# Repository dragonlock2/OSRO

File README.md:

# OSRO (Open-Source Reflow Oven)

OSRO is an ESP32-C3 powered WiFi-connected reflow oven controller designed for low cost and ease of use. Web UI is built on React JS for those aesthetics.

## Building

1. Build the web UI.
```
cd webui
npm install
npm run build
```
2. Follow the [instructions](https://docs.espressif.com/projects/esp-idf/en/latest/esp32/get-started/) to get ESP-IDF set up. Currently tested with ESP-IDF `v5.0.2`.
3. Setup the build for the firmware. Make sure to set the WiFi SSID and password under `OSRO WiFi configuration`.
```
cd firmware
get_idf
idf.py set-target esp32c3
idf.py menuconfig
```
4. Build and flash the firmware.
```
cd firmware
idf.py build
idf.py -p <serial port> flash
```

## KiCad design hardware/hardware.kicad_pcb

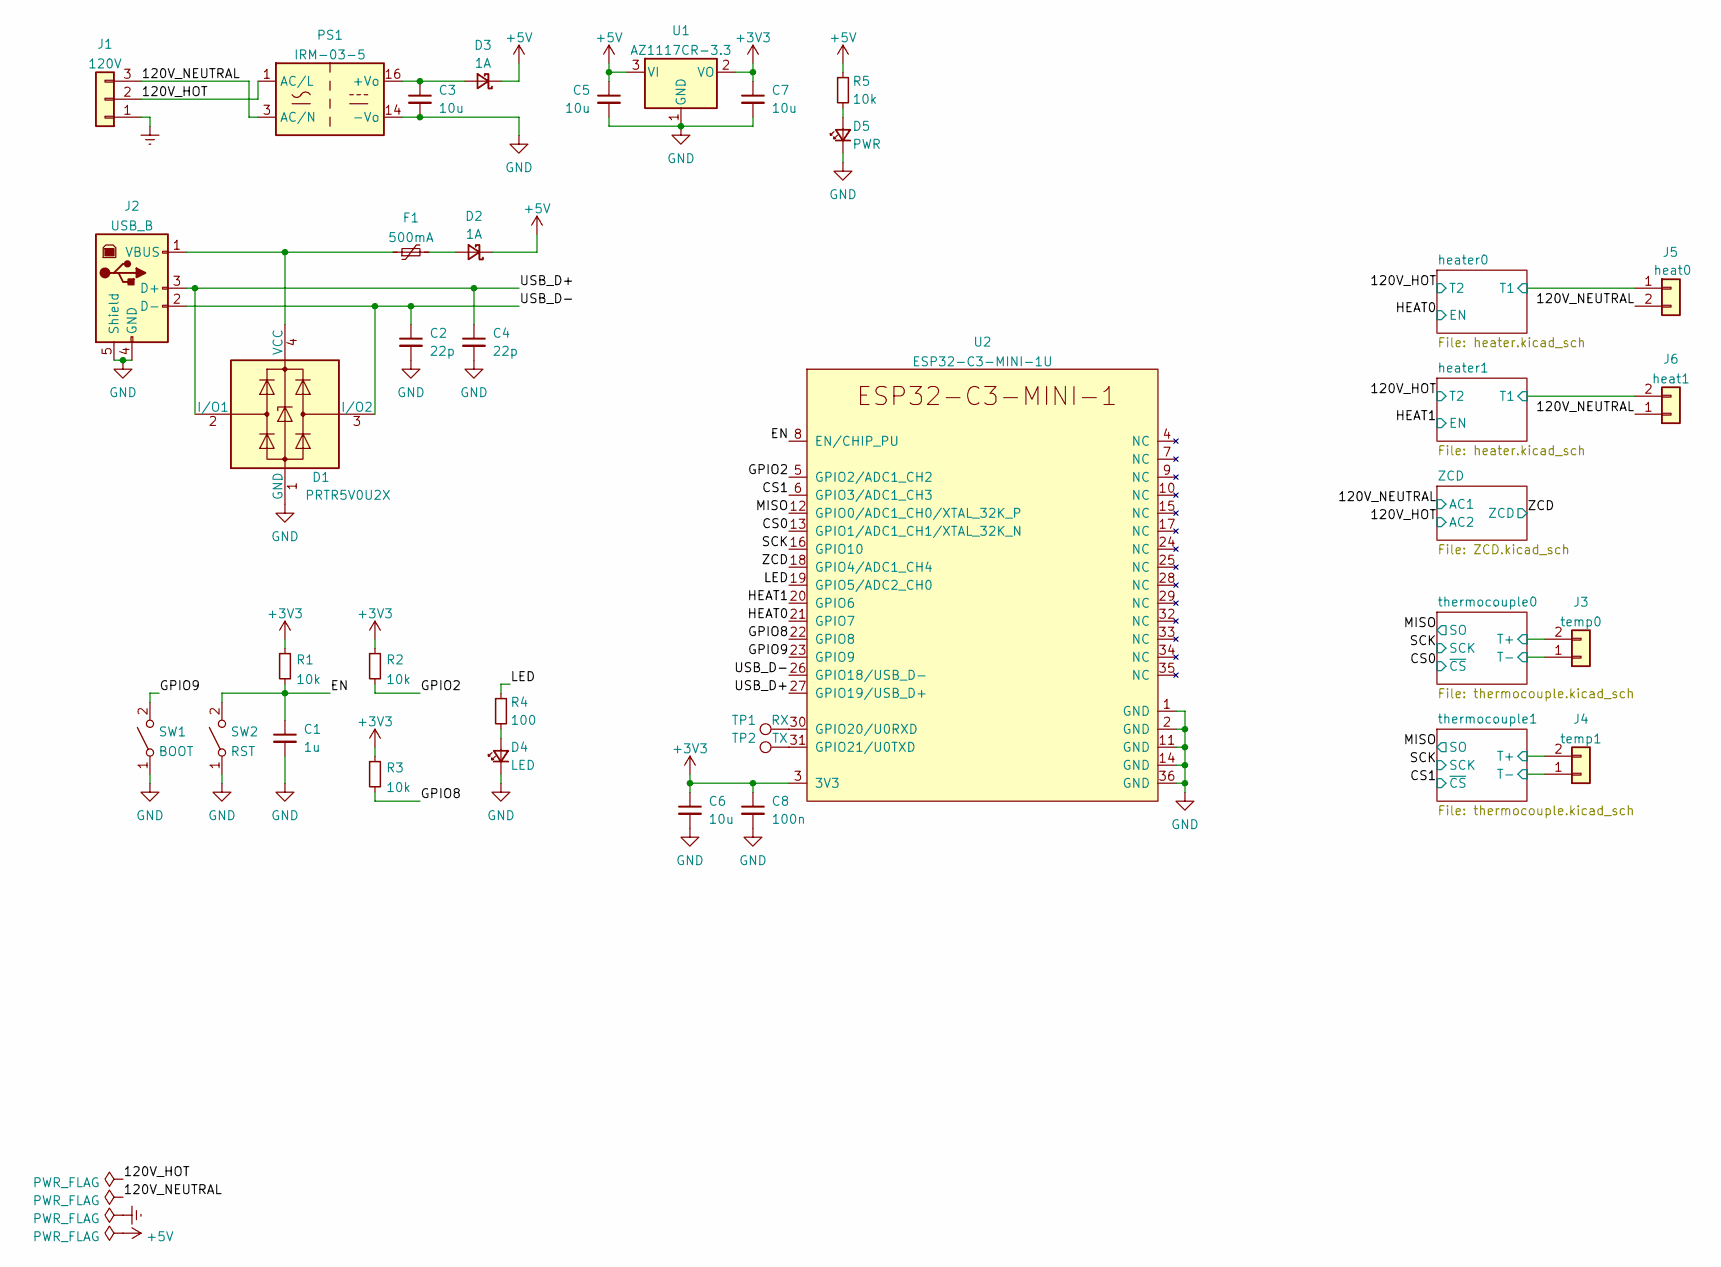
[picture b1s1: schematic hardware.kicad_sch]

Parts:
C1: 1u; C_0603_1608Metric
C2, C4: 22p; C_0603_1608Metric
C3, C5, C6, C7: 10u; C_0805_2012Metric
C8: 100n; C_0603_1608Metric
D1: PRTR5V0U2X; SOT-143
D2, D3: 1A; D_SOD-123F
D4: LED; LED_0603_1608Metric
D5: PWR; LED_0603_1608Metric
F1: 500mA; Fuse_1206_3216Metric
J1: 120V; Molex_MicroFit+_RH_1row_3pin
J2: USB_B; USB_B_TE_5787834_Vertical
J3: temp0; Molex_DuraClik_RH_2pin
J4: temp1; Molex_DuraClik_RH_2pin
J5: heat0; Molex_MicroFit+_RH_1row_2pin
J6: heat1; Molex_MicroFit+_RH_1row_2pin
PS1: IRM-03-5; Converter_ACDC_MeanWell_IRM-03-xx_THT
R1, R2, R3, R5: 10k; R_0603_1608Metric
R4: 100; R_0603_1608Metric
SW1: BOOT; SW_SPST_PTS810
SW2: RST; SW_SPST_PTS810
TP1: RX; TestPoint_Pad_D2.0mm
TP2: TX; TestPoint_Pad_D2.0mm
U1: AZ1117CR-3.3; SOT-89-3
U2: ESP32-C3-MINI-1U

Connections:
+3V3: C6.1, C7.1, C8.1, R1.1, R2.1, R3.1, U1.2 (VO), U2.3 (3V3); also elsewhere on the board
+5V: C5.1, D2.1 (K), D3.1 (K), R5.1, U1.3 (VI)
/120V_HOT: J1.2, PS1.1 (AC/L); also elsewhere on the board
/120V_NEUTRAL: J1.3, J5.2, J6.1, PS1.3 (AC/N); also elsewhere on the board
/CS0: U2.13 (GPIO1/ADC1_CH1/XTAL_32K_N); also elsewhere on the board
/CS1: U2.6 (GPIO3/ADC1_CH3); also elsewhere on the board
/EN: C1.1, R1.2, SW2.2 (B), U2.8 (EN/CHIP_PU)
/GPIO2: R2.2, U2.5 (GPIO2/ADC1_CH2)
/GPIO8: R3.2, U2.22 (GPIO8)
/GPIO9: SW1.2 (B), U2.23 (GPIO9)
/HEAT0: U2.21 (GPIO7); also elsewhere on the board
/HEAT1: U2.20 (GPIO6); also elsewhere on the board
/LED: R4.1, U2.19 (GPIO5/ADC2_CH0)
/MISO: U2.12 (GPIO0/ADC1_CH0/XTAL_32K_P); also elsewhere on the board
/SCK: U2.16 (GPIO10); also elsewhere on the board
/USB_D+: C4.1, D1.2 (I/O1), J2.3 (D+), U2.27 (GPIO19/USB_D+)
/USB_D-: C2.1, D1.3 (I/O2), J2.2 (D-), U2.26 (GPIO18/USB_D-)
/ZCD: U2.18 (GPIO4/ADC1_CH4); also elsewhere on the board
/heater0/T1: J5.1; also elsewhere on the board
/heater1/T1: J6.2; also elsewhere on the board
/thermocouple0/T+: J3.2; also elsewhere on the board
/thermocouple0/T-: J3.1; also elsewhere on the board
/thermocouple1/T+: J4.2; also elsewhere on the board
/thermocouple1/T-: J4.1; also elsewhere on the board
Earth: J1.1
GND: C1.2, C2.2, C3.2, C4.2, C5.2, C6.2, C7.2, C8.2, D1.1 (GND), D4.1 (K), D5.1 (K), J2.4 (GND), J2.5 (Shield), PS1.14 (-Vo), SW1.1 (A), SW2.1 (A), U1.1 (GND), U2.1 (GND), U2.2 (GND), U2.11 (GND), U2.14 (GND), U2.36 (GND); also elsewhere on the board
unnamed: C3.1, D3.2 (A), PS1.16 (+Vo)
unnamed: D1.4 (VCC), F1.1, J2.1 (VBUS)
unnamed: D2.2 (A), F1.2
unnamed: D4.2 (A), R4.2
unnamed: D5.2 (A), R5.2
unnamed: TP1.1, U2.30 (GPIO20/U0RXD)
unnamed: TP2.1, U2.31 (GPIO21/U0TXD)

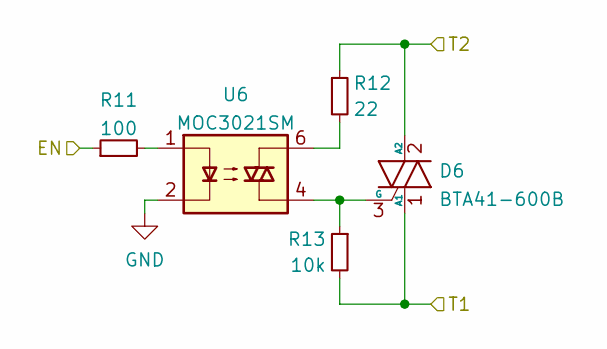
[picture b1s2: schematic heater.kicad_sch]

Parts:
D6: BTA41-600B; TO-3P-3_Horizontal_TabDown
R11: 100; R_0603_1608Metric
R12: 22; R_0603_1608Metric
R13: 10k; R_0603_1608Metric
U6: MOC3021SM; SMDIP-6_W9.53mm_Clearance8mm

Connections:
/120V_HOT: D6.2 (A2), R12.1; also elsewhere on the board
/HEAT0: R11.1; also elsewhere on the board
/heater0/T1: D6.1 (A1), R13.2; also elsewhere on the board
GND: U6.2; also elsewhere on the board
unnamed: D6.3 (G), R13.1, U6.4
unnamed: R11.2, U6.1
unnamed: R12.2, U6.6

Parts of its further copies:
D7: BTA41-600B; TO-3P-3_Horizontal_TabDown
R14: 100; R_0603_1608Metric
R15: 22; R_0603_1608Metric
R16: 10k; R_0603_1608Metric
U7: MOC3021SM; SMDIP-6_W9.53mm_Clearance8mm

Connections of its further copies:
/120V_HOT: D7.2 (A2), R15.1; also elsewhere on the board
/HEAT1: R14.1; also elsewhere on the board
/heater1/T1: D7.1 (A1), R16.2; also elsewhere on the board
GND: U7.2; also elsewhere on the board
unnamed: D7.3 (G), R16.1, U7.4
unnamed: R14.2, U7.1
unnamed: R15.2, U7.6

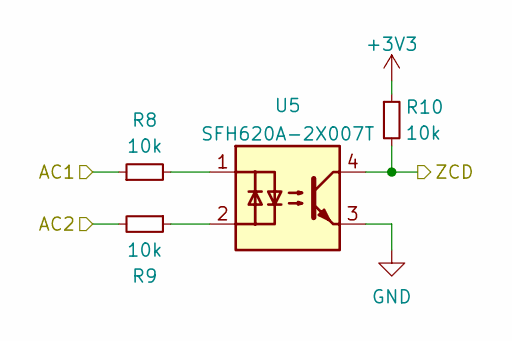
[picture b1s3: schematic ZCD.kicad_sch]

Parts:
R8, R9: 10k; R_1206_3216Metric
R10: 10k; R_0603_1608Metric
U5: SFH620A-2X007T; SMDIP-4_W9.53mm_Clearance8mm

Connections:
+3V3: R10.1; also elsewhere on the board
/120V_HOT: R9.2; also elsewhere on the board
/120V_NEUTRAL: R8.1; also elsewhere on the board
/ZCD: R10.2, U5.4; also elsewhere on the board
GND: U5.3; also elsewhere on the board
unnamed: R8.2, U5.1
unnamed: R9.1, U5.2

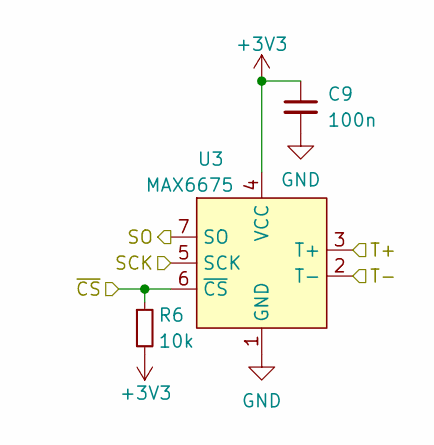
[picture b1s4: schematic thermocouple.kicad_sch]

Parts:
C9: 100n; C_0603_1608Metric
R6: 10k; R_0603_1608Metric
U3: MAX6675; SO-8_3.9x4.9mm_P1.27mm

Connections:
+3V3: C9.1, R6.2, U3.4 (VCC); also elsewhere on the board
/CS0: R6.1, U3.6 (~CS); also elsewhere on the board
/MISO: U3.7 (SO); also elsewhere on the board
/SCK: U3.5 (SCK); also elsewhere on the board
/thermocouple0/T+: U3.3 (T+); also elsewhere on the board
/thermocouple0/T-: U3.2 (T-); also elsewhere on the board
GND: C9.2, U3.1 (GND); also elsewhere on the board

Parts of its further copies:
C10: 100n; C_0603_1608Metric
R7: 10k; R_0603_1608Metric
U4: MAX6675; SO-8_3.9x4.9mm_P1.27mm

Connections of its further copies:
+3V3: C10.1, R7.2, U4.4 (VCC); also elsewhere on the board
/CS1: R7.1, U4.6 (~CS); also elsewhere on the board
/MISO: U4.7 (SO); also elsewhere on the board
/SCK: U4.5 (SCK); also elsewhere on the board
/thermocouple1/T+: U4.3 (T+); also elsewhere on the board
/thermocouple1/T-: U4.2 (T-); also elsewhere on the board
GND: C10.2, U4.1 (GND); also elsewhere on the board

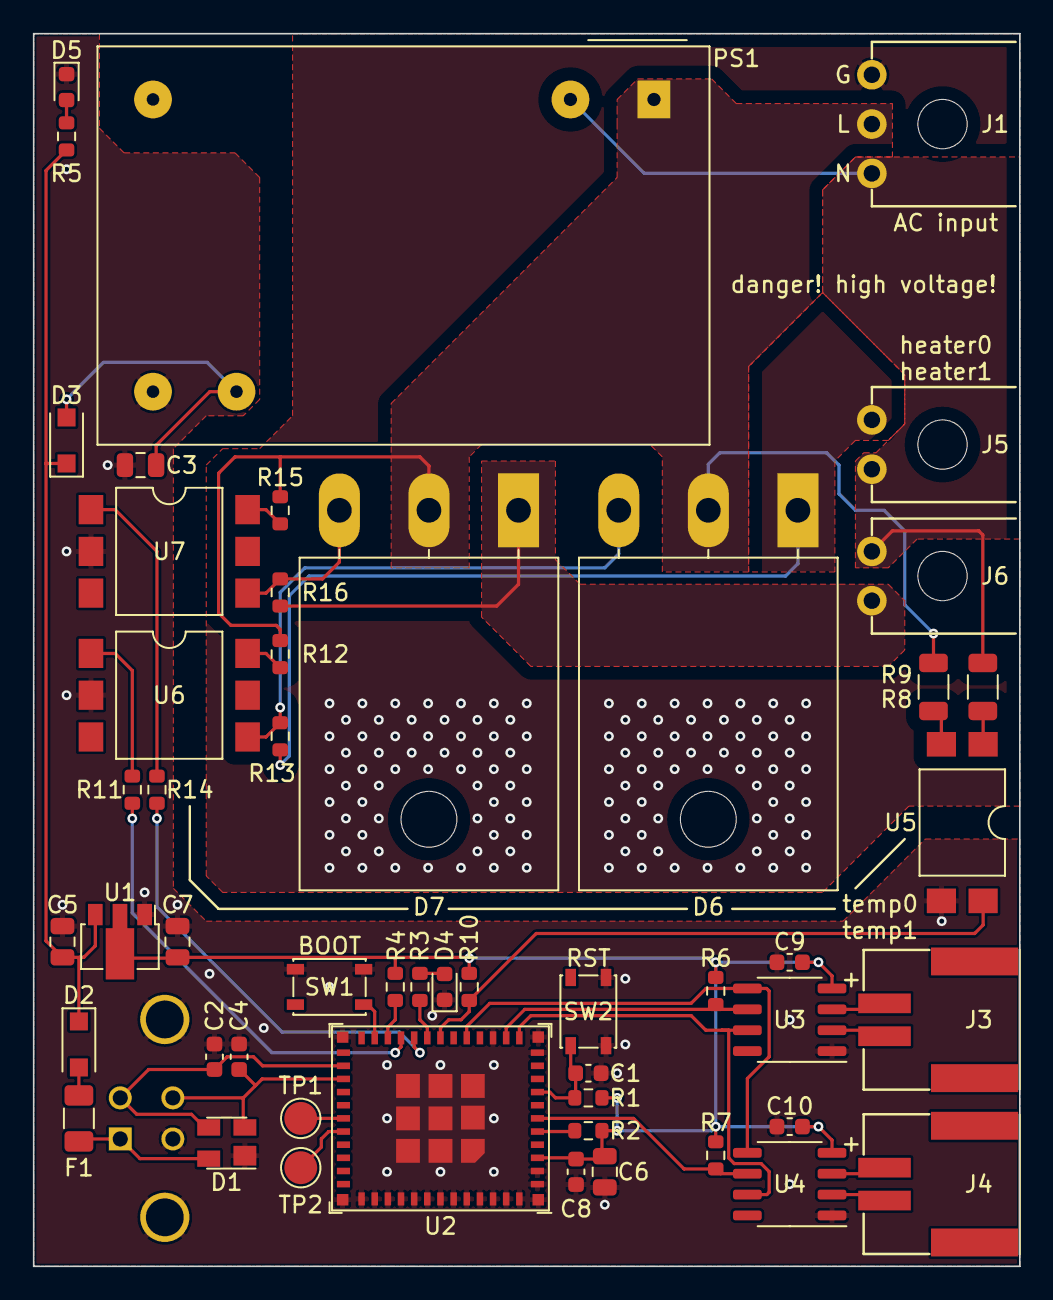
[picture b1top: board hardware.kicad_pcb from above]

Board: 2 copper layers, 60.0 x 75.0 mm, 52 parts (1 on the bottom side), 40 nets.

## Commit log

2021-12-09 added firmware start files
2021-12-09 added webui starter files
2021-12-09 UI mockup
2021-12-10 switched to React JS
2021-12-10 test live graph update
2021-12-10 optimize for mobile
2021-12-10 better xaxis
2021-12-10 shrink build size
2021-12-10 upload webui to spiffs
2021-12-10 added wifi connect
2021-12-10 added softAP option, disabled spiffs
2021-12-10 added basic file serving
2021-12-11 added mDNS
2021-12-11 added REST API
2021-12-11 finished ui integration except graph
2021-12-11 finished basic webui integration including graph
2021-12-12 slight ui update
2021-12-31 add empty board files
2021-12-31 added esp32c3 and power
2022-01-01 add thermocouple and zcd
2022-01-01 added heater
2022-01-01 assigned footprints
2022-01-01 layout WIP
2022-01-02 finished layout
2022-01-28 basic testing except heater done
2022-02-08 added bang-bang implementation
2023-06-04 update to KiCad 7
2023-06-14 WIP refactor wifi driver
2023-06-14 add WPA3 STA support
2023-06-17 basic web server
2023-07-01 added profile support
2023-07-01 working with bang-bang
2023-07-01 add PID support
2023-07-03 update ui/pid a bit
